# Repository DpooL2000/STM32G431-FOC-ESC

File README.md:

# Bare-Metal Sensorless FOC Kernel

This repository contains the hardware designs and bare-metal firmware kernels for a high-frequency sensorless FOC drive engine optimized for low-inductance UAV motors.

## System Architecture

*   **Microcontroller:** STM32G431 (170MHz Cortex-M4, utilizing internal CORDIC hardware co-processor).
*   **Target Dynamics:** 2300KV BLDC motor turning a 5-inch tri-blade propeller.
*   **Stator Identification Profile:**
    *   Phase Inductance (Ls): ~31 μH
    *   Phase Resistance (Rs): ~90 mΩ
    *   Flux Linkage (λ): ~0.00041 Wb
*   **Power Stage:** Discrete IR2101 gate drivers driving AOT418 MOSFETs, decoupled via high-speed 6N137 optocouplers for hardware shoot-through mitigation.
*   **Current Topology:** Injected low-side sensing through AD8418 current amplifiers paired with 2 mΩ shunts.

---

## Firmware Kernel Breakdown

### Core Execution Modules
*   **Pure Voltage Mode Engine:** Bypasses traditional high-lag PI current controllers to prevent phase delay at electrical frequencies exceeding 1500 Hz (30,000+ RPM).
*   **State-Space Flux Observer:** Zero-lag geometric flux estimation running at a rigid 24 kHz cycle using hardware CORDIC `get_Fast_Atan2()` calculations.
*   **Synchronous PWM Sampling:** Injected ADC conversions strictly aligned to center-count PWM timer events to read phase currents during low-side switching "quiet zones".

### The 5-Stage Spooling Sequence
1.  **OFF / CALIBRATE:** Measures operational amplifier baseline offsets.
2.  **ALIGN:** Asserts static vector to orient the rotor precisely at 0°.
3.  **OPEN_LOOP_RAMP:** Executes high-frequency blind step injection to break stator cogging torque.
4.  **FOC_BLEND:** Computes vector cross-fade from open-loop tracking to observer loop lock.
5.  **CLOSED_LOOP_FOC:** Complete handoff to pure sensorless geometric tracking.

---

## The High-RPM Non-Linear Boundary ("The Jerk")

A dedicated engineering post-mortem detailing why textbook industrial algorithms break down under microhenry, ultra-low mass environments:

*   **Cross-Coupling Destabilization:** At 40%–50% throttle, a microscopic 40 μs computational latency combined with intense reactive back-EMF cross-coupling (V = -ω * L * Iq) forces massive D-axis current (Id) spikes that derail the flux observer.
*   **Textbook Failures Documented:**
    *   **ADC Slew Limiting:** Clamping di/dt transitions starved the observer because a 31 μH coil at 12 V naturally generates an massive ~387,000 A/s rise rate.
    *   **Digital Flywheel PLLs:** Inertial filters introduced excessive mathematical phase lag, failing to track the sharp mechanical acceleration profiles of light drone props.

---

## Hardware Realities & Deadtime Distortion

*   **Pulse Devourment:** Insights on trying to execute an asymmetrical multirate loop (48 kHz PWM / 24 kHz FOC).
*   **The Math vs. Reality:** At 48 kHz, a 10% throttle command requires highly narrow 2.08 μs pulses. The gate driver's unavoidable physical deadtime (~0.5 μs) swallows a massive portion of the pulse width. This starves the stator coils of actual voltage relative to what the observer calculates, crashing the engine.
*   **Mitigation Strategy:** Reverted to a strictly synchronous 1:1 execution framework (24 kHz PWM / 24 kHz FOC) to preserve physical pulse widths.

---

## Live Telemetry Architecture

*   **The Binary Stream:** A raw, low-overhead 49-byte struct pushed at 1 kHz over a custom 2 Mbaud UART pipeline.
*   **UI Parser:** Custom PyQtGraph-driven GUI visualizing localized metrics (Id, Iq, Vd, Vq, and phase lag angle) in real-time.

---

## Repository Layout

*   **/hardware**: Layout files, optocoupler isolation circuits, and gate driver schematics.
*   **/firmware**: Clean bare-metal C modules, calibration tools, and parameter identification scripts.

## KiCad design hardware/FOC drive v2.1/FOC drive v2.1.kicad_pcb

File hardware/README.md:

# Hardware Engineering & Power Stage Architecture

This directory contains the schematic and PCB layout for the bare-metal STM32G431 ESC, designed specifically for high-frequency sensorless FOC.

## Power Stage & Isolation Topology
* **Gate Drivers:** Discrete IR2101 drivers pushing IRFZ44N MOSFETs.
* **Galvanic Isolation:** High-speed 6N137 optocouplers isolate the logic layer (STM32) from the power stage to prevent ground bounce and protect against high *di/dt* switching noise.
* **Power Management:** MP1584 Buck converter stepping the main 12V bus down to a stable 5V for logic and gate driver staging.

## Switching Dynamics & Thermal Constraints
The hardware was simulated and validated against exact MOSFET switching characteristics:
* **Miller Plateau Management:** Gate charge limits and switching losses were modeled at varying drive currents to optimize the transition through the Miller Plateau.
* **Shoot-Through Protection:** Hardware deadtime is physically characterized at 900 ns to ensure absolute safe-state switching during high/low side handoffs.

## Signal Conditioning & Analog Front End (AFE)
* **Current Sensing:** Low-side current measurement utilizing 2 mΩ shunts paired with AD8418 current sense amplifiers for precision synchronous sampling.
* **BEMF Sensing:** Phase voltages (A, B, C) are stepped down via precise resistor divider networks (10k/1k).
* **Hardware Filtering:** The BEMF signals pass through dedicated RC low-pass filters tuned to a 172.1 kHz cutoff frequency, resulting in a known, deterministic 7.9° phase lag that is compensated for in software.

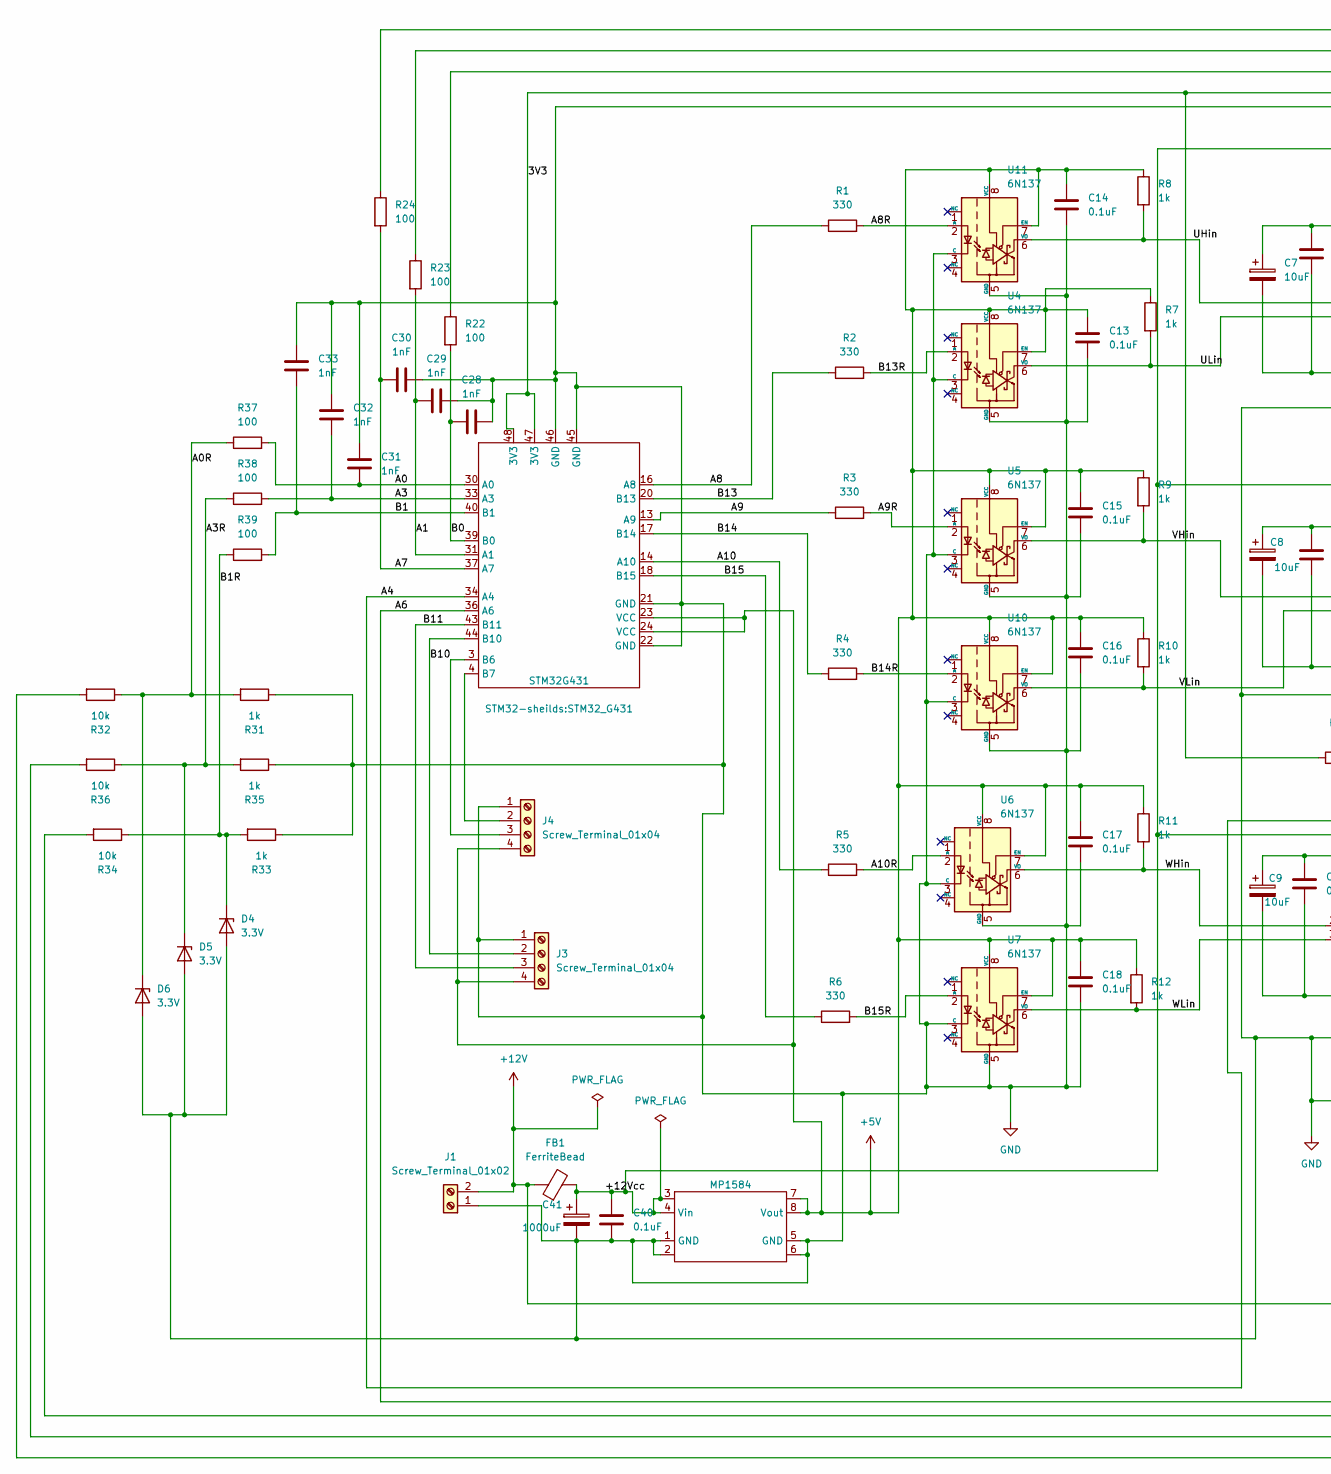
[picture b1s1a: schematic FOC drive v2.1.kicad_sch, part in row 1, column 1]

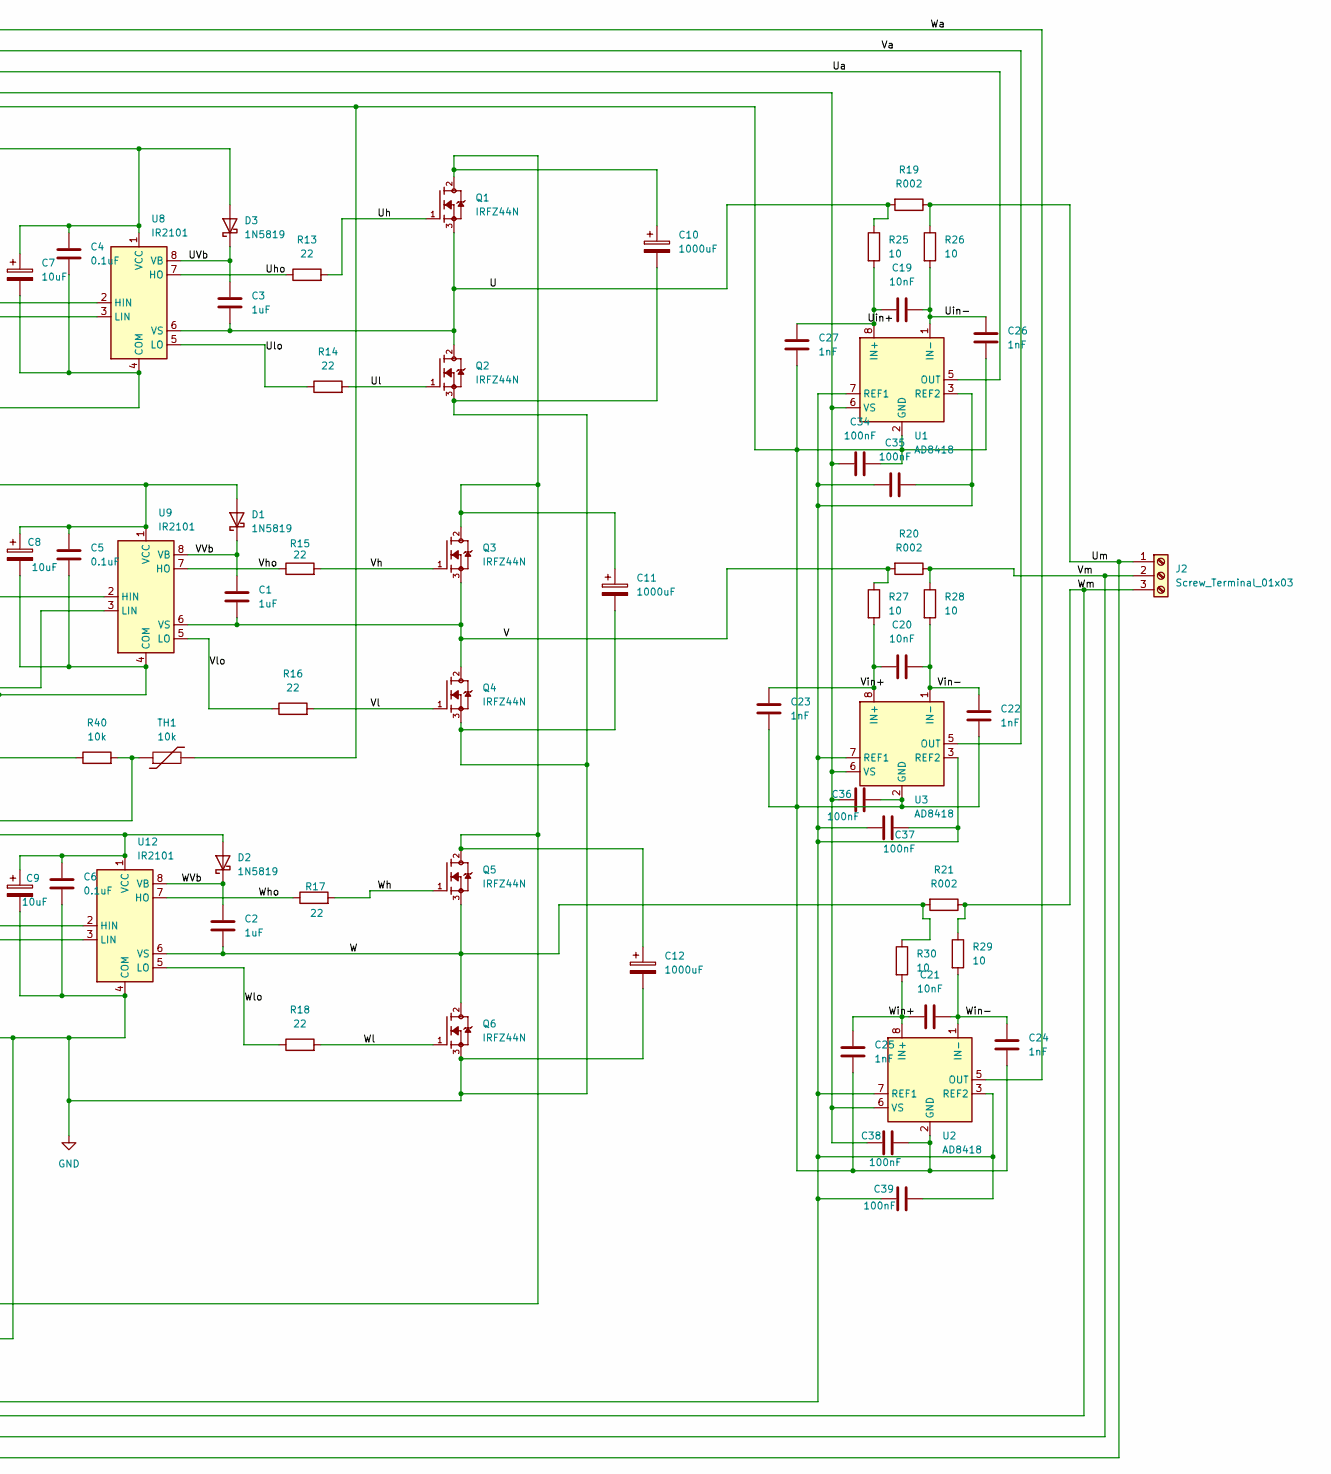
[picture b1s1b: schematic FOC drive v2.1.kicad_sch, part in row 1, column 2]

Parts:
C1, C2, C3: 1uF; C_Disc_D3.0mm_W2.0mm_P2.50mm
C4, C5, C6, C13, C14, C15, C16, C17, C18, C40: 0.1uF; C_Disc_D3.0mm_W2.0mm_P2.50mm
C7, C8, C9: 10uF; C_Radial_D5.0mm_H5.0mm_P2.00mm
C10, C11, C12: 1000uF; CP_Radial_D16.0mm_P7.50mm
C19, C20, C21: 10nF; C_Disc_D3.0mm_W2.0mm_P2.50mm
C22, C23, C24, C25, C26, C27, C28, C29, C30, C31, C32, C33: 1nF; C_Disc_D3.0mm_W2.0mm_P2.50mm
C34, C35, C36, C37, C38, C39: 100nF; C_Disc_D3.0mm_W2.0mm_P2.50mm
C41: 1000uF; CP_Radial_D5.0mm_P2.50mm
D1, D2, D3: 1N5819; D_DO-41_SOD81_P2.54mm_Vertical_AnodeUp
D4, D5, D6: 3.3V; D_DO-41_SOD81_P2.54mm_Vertical_AnodeUp
FB1: FerriteBead; L_1812_4532Metric
J1: Screw_Terminal_01x02; TerminalBlock_Phoenix_PT-1,5-2-5.0-H_1x02_P5.00mm_Horizontal
J2: Screw_Terminal_01x03; TerminalBlock_Phoenix_PT-1,5-3-5.0-H_1x03_P5.00mm_Horizontal
J3, J4: Screw_Terminal_01x04; TerminalBlock_Phoenix_MPT-0,5-4-2.54_1x04_P2.54mm_Horizontal
MP1584: MP1584
Q1, Q2, Q3, Q4, Q5, Q6: IRFZ44N; TO-220-3_Vertical; PARTREV 09/21/10
R1, R2, R3, R4, R5, R6: 330; R_Axial_DIN0204_L3.6mm_D1.6mm_P1.90mm_Vertical
R7, R8, R9, R10, R11, R12, R31, R33, R35: 1k; R_Axial_DIN0204_L3.6mm_D1.6mm_P1.90mm_Vertical
R13, R14, R15, R16, R17, R18: 22; R_Axial_DIN0204_L3.6mm_D1.6mm_P1.90mm_Vertical
R19, R20, R21: R002; R_4020_10251Metric
R22, R23, R24, R37, R38, R39: 100; R_Axial_DIN0204_L3.6mm_D1.6mm_P1.90mm_Vertical
R25, R26, R27, R28, R29, R30: 10; R_Axial_DIN0204_L3.6mm_D1.6mm_P1.90mm_Vertical
R32, R34, R36, R40: 10k; R_Axial_DIN0204_L3.6mm_D1.6mm_P1.90mm_Vertical
STM32G431: STM32_G431
TH1: 10k; R_Axial_DIN0204_L3.6mm_D1.6mm_P1.90mm_Vertical
U1, U2, U3: AD8418; SOIC-8_3.9x4.9mm_P1.27mm
U4, U5, U6, U7, U10, U11: 6N137; DIP-8_W7.62mm
U8, U9, U12: IR2101; DIP-8_W7.62mm_LongPads

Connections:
+5V: C13.1, C14.1, C15.1, C16.1, C17.1, C18.1, J3.4, J4.4, MP1584.7, MP1584.8 (Vout), R7.1, R8.1, R9.1, R10.1, R11.1, R12.1, STM32G431.23 (VCC), STM32G431.24 (VCC), U4.7 (EN), U4.8 (VCC), U5.7 (EN), U5.8 (VCC), U6.7 (EN), U6.8 (VCC), U7.7 (EN), U7.8 (VCC), U10.7 (EN), U10.8 (VCC), U11.7 (EN), U11.8 (VCC)
+12V: C10.1, C11.1, C12.1, FB1.1, J1.2, Q1.2, Q3.2, Q5.2
/3V3: C34.2, C36.2, C38.2, R40.1, STM32G431.47 (3V3), STM32G431.48 (3V3), U1.6 (VS), U2.6 (VS), U3.6 (VS)
/+12Vcc: C4.1, C5.1, C6.1, C7.1, C8.1, C9.1, C40.1, C41.1, D1.2 (A), D2.2 (A), D3.2 (A), FB1.2, MP1584.3, MP1584.4 (Vin), U8.1 (VCC), U9.1 (VCC), U12.1 (VCC)
/A0: C31.1, R37.2, STM32G431.30 (A0)
/A0R: D6.1 (K), R31.2, R32.1, R37.1
/A1: C29.1, R23.2, STM32G431.31 (A1)
/A3: C32.1, R38.2, STM32G431.33 (A3)
/A3R: D5.1 (K), R35.2, R36.1, R38.1
/A4: R40.2, STM32G431.34 (A4), TH1.1
/A6: C35.1, C35.2, C37.1, C37.2, C39.1, C39.2, STM32G431.36 (A6), U1.3 (REF2), U1.7 (REF1), U2.3 (REF2), U2.7 (REF1), U3.3 (REF2), U3.7 (REF1)
/A7: C30.1, R24.2, STM32G431.37 (A7)
/A8: R1.1, STM32G431.16 (A8)
/A8R: R1.2, U11.2 (A)
/A9: R3.1, STM32G431.13 (A9)
/A9R: R3.2, U5.2 (A)
/A10: R5.1, STM32G431.14 (A10)
/A10R: R5.2, U6.2 (A)
/B0: C28.1, R22.2, STM32G431.39 (B0)
/B1: C33.1, R39.2, STM32G431.40 (B1)
/B1R: D4.1 (K), R33.2, R34.1, R39.1
/B10: J3.2, STM32G431.44 (B10)
/B11: J3.3, STM32G431.43 (B11)
/B13: R2.1, STM32G431.20 (B13)
/B13R: R2.2, U4.2 (A)
/B14: R4.1, STM32G431.17 (B14)
/B14R: R4.2, U10.2 (A)
/B15: R6.1, STM32G431.18 (B15)
/B15R: R6.2, U7.2 (A)
/U: C3.2, Q1.3, Q2.2, R19.2, R25.1, U8.6 (VS)
/UHin: R8.2, U8.2 (HIN), U11.6 (VO)
/ULin: R7.2, U4.6 (VO), U8.3 (LIN)
/UVb: C3.1, D3.1 (K), U8.8 (VB)
/Ua: R22.1, U1.5 (OUT)
/Uh: Q1.1, R13.2
/Uho: R13.1, U8.7 (HO)
/Uin+: C19.2, C27.1, R25.2, U1.8 (IN+)
/Uin-: C19.1, C26.1, R26.2, U1.1 (IN-)
/Ul: Q2.1, R14.2
/Ulo: R14.1, U8.5 (LO)
/Um: J2.1, R19.1, R26.1, R32.2
/V: C1.2, Q3.3, Q4.2, R20.2, R27.1, U9.6 (VS)
/VHin: R9.2, U5.6 (VO), U9.2 (HIN)
/VLin: R10.2, U9.3 (LIN), U10.6 (VO)
/VVb: C1.1, D1.1 (K), U9.8 (VB)
/Va: R23.1, U3.5 (OUT)
/Vh: Q3.1, R15.2
/Vho: R15.1, U9.7 (HO)
/Vin+: C20.2, C23.1, R27.2, U3.8 (IN+)
/Vin-: C20.1, C22.1, R28.2, U3.1 (IN-)
/Vl: Q4.1, R16.2
/Vlo: R16.1, U9.5 (LO)
/Vm: J2.2, R20.1, R28.1, R36.2
/W: C2.2, Q5.3, Q6.2, R21.2, R30.1, U12.6 (VS)
/WHin: R11.2, U6.6 (VO), U12.2 (HIN)
/WLin: R12.2, U7.6 (VO), U12.3 (LIN)
/WVb: C2.1, D2.1 (K), U12.8 (VB)
/Wa: R24.1, U2.5 (OUT)
/Wh: Q5.1, R17.2
/Who: R17.1, U12.7 (HO)
/Win+: C21.2, C25.1, R30.2, U2.8 (IN+)
/Win-: C21.1, C24.1, R29.2, U2.1 (IN-)
/Wl: Q6.1, R18.2
/Wlo: R18.1, U12.5 (LO)
/Wm: J2.3, R21.1, R29.1, R34.2
GND: C4.2, C5.2, C6.2, C7.2, C8.2, C9.2, C10.2, C11.2, C12.2, C13.2, C14.2, C15.2, C16.2, C17.2, C18.2, C22.2, C23.2, C24.2, C25.2, C26.2, C27.2, C28.2, C29.2, C30.2, C31.2, C32.2, C33.2, C34.1, C36.1, C38.1, C40.2, C41.2, D4.2 (A), D5.2 (A), D6.2 (A), J1.1, J3.1, J4.1, MP1584.1 (GND), MP1584.2, MP1584.5 (GND), MP1584.6, Q2.3, Q4.3, Q6.3, R31.1, R33.1, R35.1, STM32G431.21 (GND), STM32G431.22 (GND), STM32G431.45 (GND), STM32G431.46 (GND), TH1.2, U1.2 (GND), U2.2 (GND), U3.2 (GND), U4.3 (C), U4.5 (GND), U5.3 (C), U5.5 (GND), U6.3 (C), U6.5 (GND), U7.3 (C), U7.5 (GND), U8.4 (COM), U9.4 (COM), U10.3 (C), U10.5 (GND), U11.3 (C), U11.5 (GND), U12.4 (COM)
unnamed: J4.2, STM32G431.4 (B7)
unnamed: J4.3, STM32G431.3 (B6)

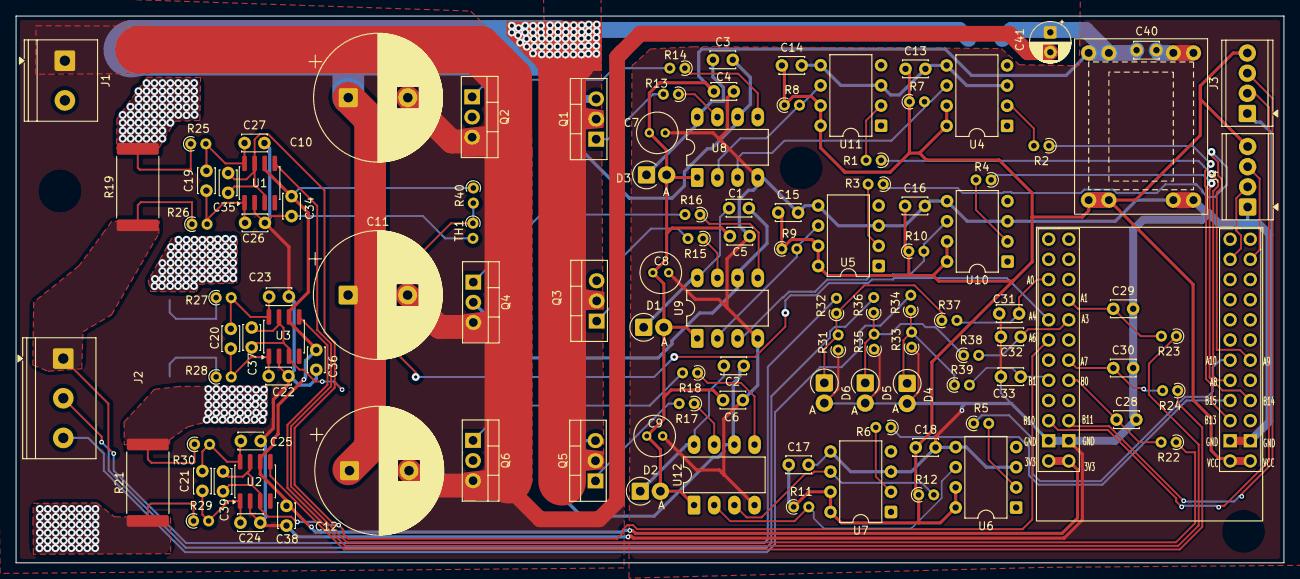
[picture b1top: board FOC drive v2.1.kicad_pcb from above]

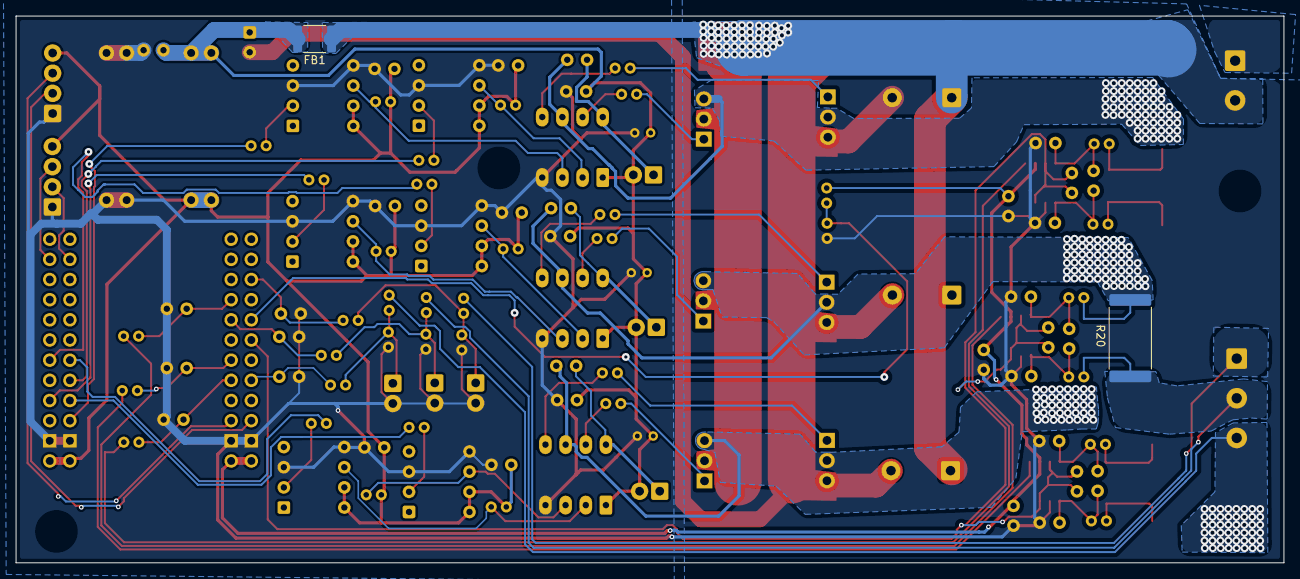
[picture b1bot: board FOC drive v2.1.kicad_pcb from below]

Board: 2 copper layers, 159.7 x 68.9 mm, 113 parts (2 on the bottom side), 68 nets.
